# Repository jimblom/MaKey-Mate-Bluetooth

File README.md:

# MaKey Mate Bluetooth

This is example code for the [MaKey MaKey](https://www.sparkfun.com/products/11511) and [Bluetooth Mate for the MaKey MaKey](https://www.sparkfun.com/products/11378) combo. The goal is to make the combination of both boards feel exactly like the MaKey MaKey...but wireless. Set your banana keyboards and play-doh controllers free!

This example code should be taken as just that... *example* code. It might not work perfectly for everyone's project, but I hope I've made everything it does transparent enough for you to be able to tailor it to your needs.

This code builds on the original [MaKey MaKey code](https://github.com/sparkfun/MaKeyMaKey), written by Jay Silver, Eric Rosenbaum, and I. I've added two files - makeyMate.cpp and makeyMate.h - which handle all of the communication and setup with the RN-42 HID bluetooth module. The main ino file remains mostly unchanged, the major changes were turning any `keyboard.press` and `mouse.move` type commands to `makeyMate` class commands.

## What's Here?

* **maKeyMate_BT** directory - This houses the Arduino example code. Standard to the Arduino file directory structure, the main .ino file shares the same name as the directory.
* **hardware** - This houses the Eagle design files for the schematic and PCB of the Bluetooth Mate for MaKey MaKey.
* [wiki](https://github.com/jimblom/MaKey-Mate-Bluetooth/wiki) - Step-by-step installation guide for the Bluetooth Mate for MaKey MaKey

## License

This project is released as **beerware**. Feel free to use it, with or without attribution, in your own projects. If you find it helpful, buy me a beer (alcoholic or root variety are both fine :) next time we meet up.

## Issues, forking, troubleshooting, and the wiki

If you have any trouble with this code, or are looking for a step-by-step guide, please check out the [wiki](https://github.com/jimblom/MaKey-Mate-Bluetooth/wiki) first. I'll be monitoring the issues, so if the wiki doesn't solve your problem, please post away there.

- Jim Lindblom
SparkFun Electronics
October 24, 2012

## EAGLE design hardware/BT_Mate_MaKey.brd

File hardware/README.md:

# MaKey Mate BT Hardware Design Files

These files were created using Eagle 6.2.0.

## What's Here?

* BT_Mate_MaKey.sch - The schematic file for the Bluetooth Mate for MaKey MaKey.
* BT_Mate_MaKey.brd - The PCB design file for the Bluetooth Mate for MaKey MaKey.

Both files require Eagle to view and modify. There is a freeware version of Eagle.

## License

These hardware design files are released as open source hardware under the [Creative Commons Attribution-ShareAlike license](http://creativecommons.org/licenses/by-sa/3.0/). Please feel free to use, reuse, remix, resell this design however you see fit. We do ask that you maintain attribution, retain this license, and let us know what you've improved!

- Jim Lindblom
SparkFun Electronics
October 24, 2012

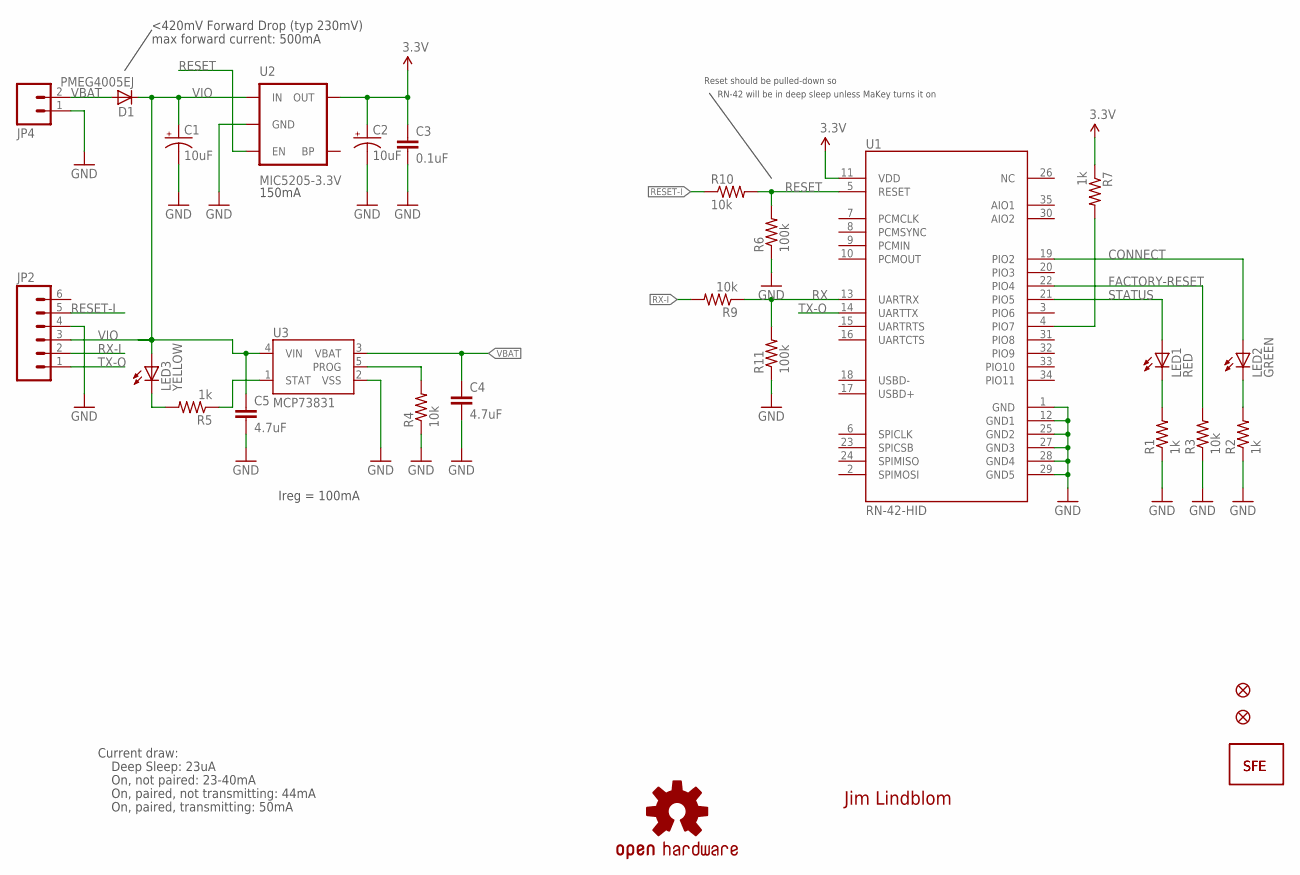
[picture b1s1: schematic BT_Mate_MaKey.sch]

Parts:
C1, C2: 10uF; EIA3216
C3: 0.1uF; 0402-CAP
C4, C5: 4.7uF; 0402-CAP
D1: PMEG4005EJ; SOD-323
JP1: LOGO-SFESK; SFE-LOGO-FLAME
JP2: M06SIP; 1X06
JP3: LOGO-SFENW2; SFE-NEW-WEB
JP4: M02-JST-2MM-SMT; JST-2-SMD
JP5, JP6: FIDUCIALUFIDUCIAL; MICRO-FIDUCIAL
LED1: RED; LED-0603
LED2: GREEN; LED-0603
LED3: YELLOW; LED-0603
R1, R2, R5, R7: 1k; 0402-RES
R3, R4, R9, R10: 10k; 0402-RES
R6, R11: 100k; 0402-RES
U1: RN-42-HID; RN41
U2: MIC5205-3.3V; SOT23-5
U3: MCP73831; SOT23-5
U$2: OSHW-LOGOS; OSHW-LOGO-S

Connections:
3.3V: C2.A (+), C3.1, R7.1, U1.11 (VDD), U2.5 (OUT)
CONNECT: LED2.A, U1.19 (PIO2)
FACTORY-RESET: R3.2, U1.22 (PIO4)
GND: C1.C (-), C2.C (-), C3.2, C4.2, C5.2, JP2.4, JP4.1 (2), R1.1, R2.1, R3.1, R4.1, R6.1, R11.1, U1.1 (GND), U1.12 (GND1), U1.25 (GND2), U1.27 (GND3), U1.28 (GND4), U1.29 (GND5), U2.2 (GND), U3.2 (VSS)
unnamed: R7.2, U1.4 (PIO7)
unnamed: LED1.C, R1.2
unnamed: LED2.C, R2.2
unnamed: R4.2, U3.5 (PROG)
unnamed: R5.1, U3.1 (STAT)
unnamed: LED3.C, R5.2
RESET: R6.2, R10.2, U1.5 (RESET), U2.3 (EN)
RESET-I: JP2.5, R10.1
RX: R9.1, R11.2, U1.13 (UARTRX)
RX-I: JP2.2, R9.2
STATUS: LED1.A, U1.21 (PIO5)
TX-O: JP2.1, U1.14 (UARTTX)
VBAT: C4.1, D1.2 (A), JP4.2 (1), U3.3 (VBAT)
VIO: C1.A (+), C5.1, D1.1 (C), JP2.3, LED3.A, U2.1 (IN), U3.4 (VIN)

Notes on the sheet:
150mA
Ireg = 100mA
Jim Lindblom
Reset should be pulled-down so
RN-42 will be in deep sleep unless MaKey turns it on
<420mV Forward Drop (typ 230mV)
Current draw:
Deep Sleep: 23uA
On, not paired: 23-40mA
On, paired, not transmitting: 44mA
On, paired, transmitting: 50mA
max forward current: 500mA

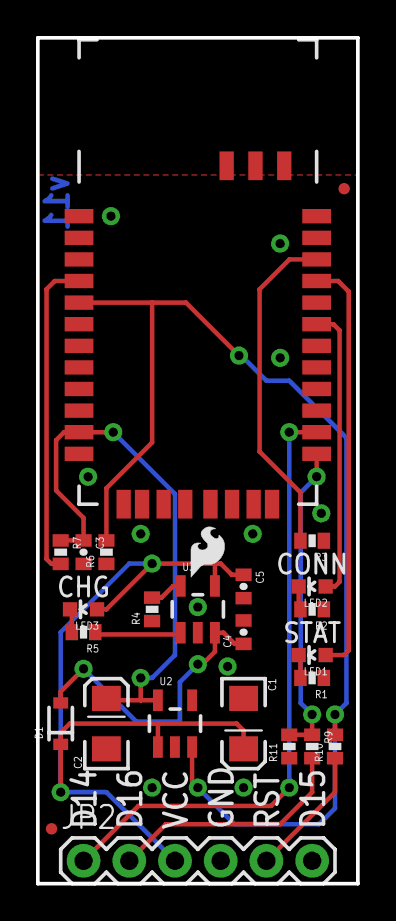
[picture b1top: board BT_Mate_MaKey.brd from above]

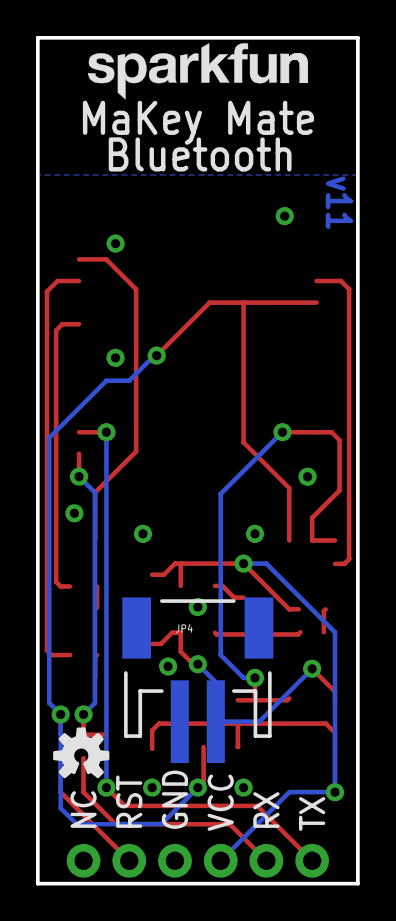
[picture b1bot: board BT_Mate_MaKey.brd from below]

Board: 2 copper layers, 17.8 x 47.0 mm, 29 parts (3 on the bottom side), 18 nets.

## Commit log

2012-10-04 Initial working commit.
2012-10-08 Revising directory structure (putting .ino in makeyMate_BT folder) Fixing some whitespace, comments Removed unnecessary Serial.print calls
2012-10-08 moving files to maKeyMate_BT directory
2012-10-17 Fixes to mode and authentication settings Think this will make it work on phones and Macs more reliably
2012-10-23 More robust two-way serial communication bluetooth.println's should have been print(...) followed by write('\r'). More comments!
2012-10-24 minor functionality changes. mostly...comments!
2012-10-24 Initial commit of hardware design files. Minor comment changes. Added some readme.md's, first attempt at markdown readmes.
2012-11-01 Generalizing the default name
    Whitespace and comment changes too.

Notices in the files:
parts and their libraries:
SparkFun-RF: Licensing: CC v3.0 Share-Alike You are welcome to use this library for commercial purposes.
SparkFun-Aesthetics: Released under the Creative Commons
